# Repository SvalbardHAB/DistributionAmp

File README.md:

# DistributionAmp
434MHz/868MHz LoRa distribution amplifier (BPF and LNA followed by splitter)

This is a simple board designed to improve the performance of a LoRa system, as well as allowing multiple
receivers at multiple frequencies or for redundancy (e.g. we used this for a one-off HAB experiment
opportunity).

It features:

 - Input SAW filter for out-of-band noise rejection (e.g. 800MHz 4G) with ESD protection
 - MAAL-010704 (0.8dB NF, 20dB gain) LNA
 - Inductive splitter to four outputs with SMA connectors
 - Low noise 3V LDO powering the LNA

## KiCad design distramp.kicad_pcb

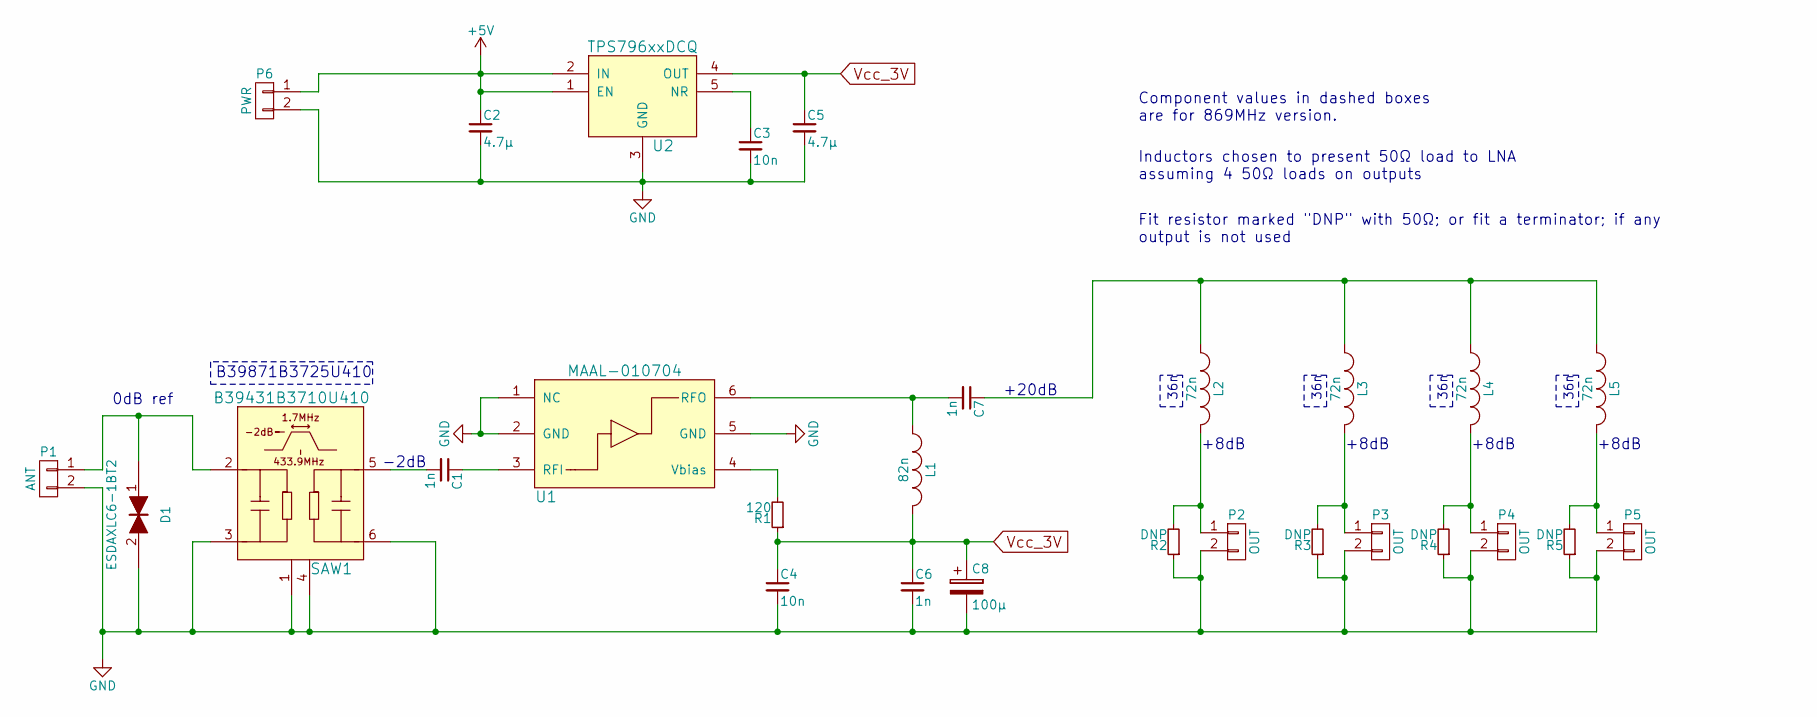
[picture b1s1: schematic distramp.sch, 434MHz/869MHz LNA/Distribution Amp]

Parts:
C1, C6, C7: 1n; C_0402
C2, C5: 4.7µ; C_0805
C3, C4: 10n; C_0402
C8: 100µ; TantalC_SizeD_EIA-7343_Reflow
D1: ESDAXLC6-1BT2; R_0402
L1: 82n; R_0402
L2, L3, L4, L5: 72n; R_0402
P1: ANT; RFcon
P2, P3, P4, P5: OUT; RFcon
P6: PWR; Pin_Header_Straight_1x02
R1: 120; R_0402
R2, R3, R4, R5: DNP; R_0402
SAW1: B39431B3710U410; SAW-DCC6C
U1: MAAL-010704; SC-70-6_Handsoldering
U2: TPS796xxDCQ; SOT-223-6

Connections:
+5V: C2.1, P6.1, U2.1 (EN), U2.2 (IN)
GND: C2.2, C3.2, C4.2, C5.2, C6.2, C8.2, D1.2, P1.2, P2.2, P3.2, P4.2, P5.2, P6.2, R2.1, R3.1, R4.1, R5.1, SAW1.1 (GND), SAW1.3 (GND), SAW1.4 (GND), SAW1.6 (GND), U1.1 (NC), U1.2 (GND), U1.5 (GND), U2.3 (GND)
unnamed: C1.1, U1.3 (RFI)
unnamed: C1.2, SAW1.5 (OUT)
unnamed: C3.1, U2.5 (NR)
unnamed: C7.1, L2.1, L3.1, L4.1, L5.1
unnamed: C7.2, L1.1, U1.6 (RFO)
unnamed: D1.1, P1.1, SAW1.2 (IN)
unnamed: L2.2, P2.1, R2.2
unnamed: L3.2, P3.1, R3.2
unnamed: L4.2, P4.1, R4.2
unnamed: L5.2, P5.1, R5.2
unnamed: R1.2, U1.4 (Vbias)
Vcc_3V: C4.1, C5.1, C6.1, C8.1, L1.2, R1.1, U2.4 (OUT)

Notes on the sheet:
Inductors chosen to present 50Ω load to LNA assuming 4 50Ω loads on outputs
Fit resistor marked "DNP" with 50Ω; or fit a terminator; if any output is not used
0dB ref
-2dB
+20dB
+8dB
B39871B3725U410
36n
Component values in dashed boxes are for 869MHz version.

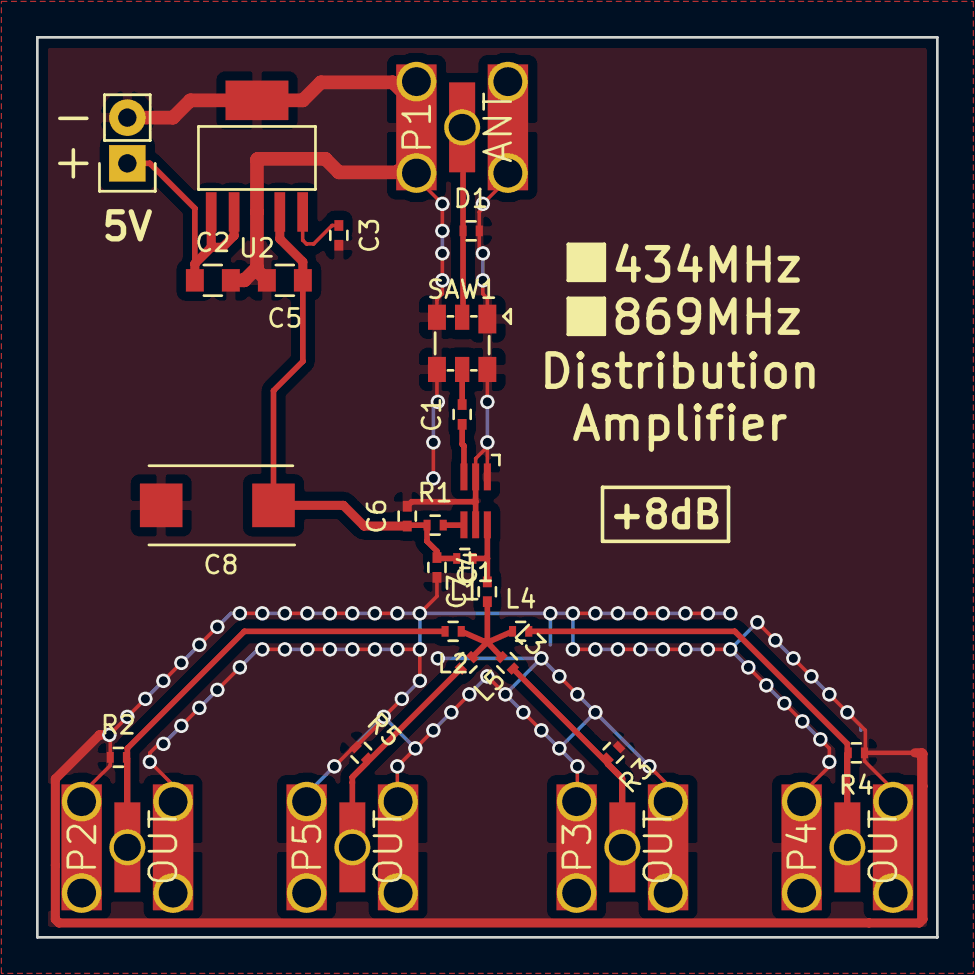
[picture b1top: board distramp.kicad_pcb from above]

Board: 4 copper layers, 50.0 x 50.0 mm, 28 parts (0 on the bottom side), 14 nets.

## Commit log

2016-07-12 RF part of schematic done
2016-07-12 Assign footprints, place parts on PCB
2016-07-12 RF routed
2016-07-12 More PCB work
2016-07-13 Add Power Connector
2016-07-15 Specify 869MHz component values
2016-07-15 Export Gerbers for production by Elecrow (need checking)
